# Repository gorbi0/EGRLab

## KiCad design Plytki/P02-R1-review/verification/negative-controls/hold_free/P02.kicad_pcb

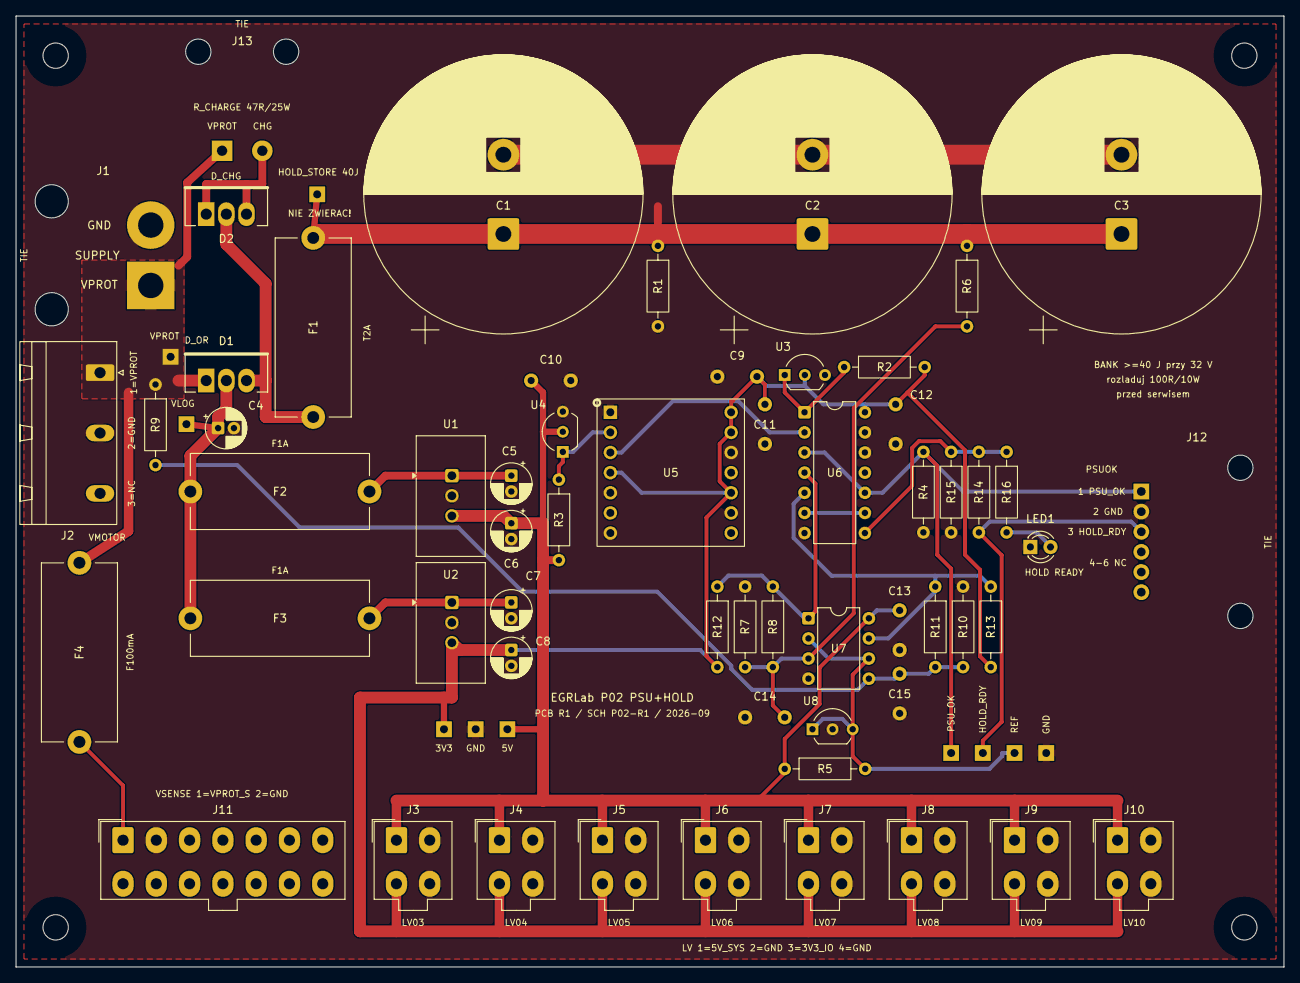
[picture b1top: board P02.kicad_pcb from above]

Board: 2 copper layers, 160.0 x 120.0 mm, 73 parts (0 on the bottom side), 24 nets.

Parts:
C1, C2, C3: 22000u / 35V; CP_Radial_D35.0mm_P10.00mm_SnapIn
C4: 22u / 50V; CP_Radial_D5.0mm_P2.00mm
C5, C7: 10u / 50V; CP_Radial_D5.0mm_P2.00mm
C6, C8: 22u / 16V; CP_Radial_D5.0mm_P2.00mm
C9, C10, C11, C12, C13, C14, C15: 100nF / X7R; C_Vishay_K15_H5_P5
D1: STPS20100CT / D_OR; TO220_3_P2.54_Drill1.4
D2: STPS20100CT / D_CHARGE; TO220_3_P2.54_Drill1.4
F1: T2A / 5x20 DC; Fuseholder_Cylinder-5x20mm_Stelvio-Kontek_PTF78_Horizontal_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
F2, F3: 1A / 5x20; Fuseholder_Cylinder-5x20mm_Stelvio-Kontek_PTF78_Horizontal_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
F4: F100mA / 5x20; Fuseholder_Cylinder-5x20mm_Stelvio-Kontek_PTF78_Horizontal_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
H1, H2, H3, H4: M3 NPTH
J1: SUPPLY / soldered wires; Pigtail_PWR_2x2.5mm2
J2: VMOTOR / GMSTBA 3p 7.62; PhoenixContact_GMSTBA_2,5_3-G-7,62_1x03_P7.62mm_Horizontal
J3: LV03 / Mini-Fit Jr 4p; Molex_Mini-Fit_Jr_5566-04A_2x02_P4.20mm_Vertical
J4: LV04 / Mini-Fit Jr 4p; Molex_Mini-Fit_Jr_5566-04A_2x02_P4.20mm_Vertical
J5: LV05 / Mini-Fit Jr 4p; Molex_Mini-Fit_Jr_5566-04A_2x02_P4.20mm_Vertical
J6: LV06 / Mini-Fit Jr 4p; Molex_Mini-Fit_Jr_5566-04A_2x02_P4.20mm_Vertical
J7: LV07 / Mini-Fit Jr 4p; Molex_Mini-Fit_Jr_5566-04A_2x02_P4.20mm_Vertical
J8: LV08 / Mini-Fit Jr 4p; Molex_Mini-Fit_Jr_5566-04A_2x02_P4.20mm_Vertical
J9: LV09 / Mini-Fit Jr 4p; Molex_Mini-Fit_Jr_5566-04A_2x02_P4.20mm_Vertical
J10: LV10 / Mini-Fit Jr 4p; Molex_Mini-Fit_Jr_5566-04A_2x02_P4.20mm_Vertical
J11: VSENSE / Mini-Fit Jr 14p; Molex_Mini-Fit_Jr_5566-14A_2x07_P4.20mm_Vertical
J12: PSUOK / soldered ribbon; Pigtail_PSUOK_6x_P2.54
J13: R_CHARGE / wires; Pigtail_RCHARGE_2xAWG20
LED1: GREEN 3mm / HOLD READY; LED_D3.0mm
R1: 4K7 / 1%; R_Axial_DIN0207_L6.3mm_D2.5mm_P10.16mm_Horizontal
R2, R3, R4, R12, R13, R15: 10K / 1%; R_Axial_DIN0207_L6.3mm_D2.5mm_P10.16mm_Horizontal
R5, R14, R16: 1K / 1%; R_Axial_DIN0207_L6.3mm_D2.5mm_P10.16mm_Horizontal
R6: 267K / 1%; R_Axial_DIN0207_L6.3mm_D2.5mm_P10.16mm_Horizontal
R7, R10: 100K / 1%; R_Axial_DIN0207_L6.3mm_D2.5mm_P10.16mm_Horizontal
R8, R11: 2M2 / 1%; R_Axial_DIN0207_L6.3mm_D2.5mm_P10.16mm_Horizontal
R9: 348K / 1%; R_Axial_DIN0207_L6.3mm_D2.5mm_P10.16mm_Horizontal
TP1: VPROT; TestPad_1
TP2: VLOG_RES; TestPad_1
TP3: HOLD_STORE; TestPad_1
TP4: 5V_SYS; TestPad_1
TP5: 3V3_IO; TestPad_1
TP6, TP10: GND; TestPad_1
TP7: PSU_OK; TestPad_1
TP8: HOLD_READY; TestPad_1
TP9: REF25; TestPad_1
U1: TSR 2-2450; Converter_DCDC_TRACO_TSR2-xxxx_THT
U2: TSR 2-2433; Converter_DCDC_TRACO_TSR2-xxxx_THT
U3: MCP120-300DI/TO; TO-92_Inline_Wide
U4: MCP120-450DI/TO; TO-92_Inline_Wide
U5: 74LVC125A / SO14 adapter; Adapter_SO14_DIP14_W15.24_Kamami575068
U6: SN74HC08N; DIP-14_W7.62mm
U7: LM2903P; DIP-8_W7.62mm
U8: TL431BILP; TO-92_Inline_Wide

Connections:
3V3_IO: C8.1, C9.1, C11.1, C12.1, J3.3, J4.3, J5.3, J6.3, J7.3, J8.3, J9.3, J10.3, R2.2, R12.2, R13.2, TP5.1, U2.3, U3.2, U5.4, U5.10, U5.13, U5.14, U6.14
5V_SYS: C6.1, C10.1, C13.1, J3.1, J4.1, J5.1, J6.1, J7.1, J8.1, J9.1, J10.1, R3.2, R5.1, TP4.1, U1.3, U4.2, U7.8
/CHARGE_D: D2.1, D2.3, J13.2
/HOLD_FUSED: D1.3, D2.2, F1.1
/MON/HOLD_READY: J12.3, R14.2, TP8.1
/MON/P02_BANK_DIV: C14.1, R6.2, R7.1, R8.2, U7.3
/MON/P02_BANK_OK: R8.1, R12.1, U6.4, U7.1
/MON/P02_HOLD_QUAL: U6.6, U6.9
/MON/P02_HOLD_READY_INT: R14.1, R15.1, R16.1, U6.8
/MON/P02_LED_A: LED1.2, R16.2
/MON/P02_REF25: R5.2, TP9.1, U7.2, U7.6, U8.1, U8.3
/MON/P02_SUP3_N: R2.1, U3.1, U6.1
/MON/P02_SUP5_N: U5.3, U6.2
/MON/P02_SUP5_RAW: R3.1, U4.1, U5.2
/MON/P02_VPROT_DIV: C15.1, R9.2, R10.1, R11.2, U7.5
/MON/P02_VPROT_OK: R11.1, R13.1, U6.5, U7.7
/MON/PSU_OK: J12.1, R4.1, TP7.1, U6.3, U6.10
/P02_VIN_DC5: C5.1, F2.2, U1.1
/P02_VIN_DC33: C7.1, F3.2, U2.1
/VLOG_RES: C4.1, D1.2, F2.1, F3.1, TP2.1
/VPROT_SENSE: F4.2, J11.1
GND: C1.2, C2.2, C3.2, C4.2, C5.2, C6.2, C7.2, C8.2, C9.2, C10.2, C11.2, C12.2, C13.2, C14.2, C15.2, J1.2, J2.2, J3.2, J3.4, J4.2, J4.4, J5.2, J5.4, J6.2, J6.4, J7.2, J7.4, J8.2, J8.4, J9.2, J9.4, J10.2, J10.4, J11.2, J12.2, LED1.1, R1.2, R4.2, R7.2, R10.2, R15.2, TP6.1, TP10.1, U1.2, U2.2, U3.3, U4.3, U5.1, U5.5, U5.7, U5.9, U5.12, U6.7, U6.12, U6.13, U7.4, U8.2
HOLD_STORE: C1.1, C2.1, C3.1, F1.2, R1.1, R6.1, TP3.1
VPROT: D1.1, F4.1, J1.1, J2.1, J13.1, R9.1, TP1.1
